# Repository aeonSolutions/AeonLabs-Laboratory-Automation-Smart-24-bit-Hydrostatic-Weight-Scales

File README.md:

[PCB-Prototyping-Catalogue](https://github.com/aeonSolutions/PCB-Prototyping-Catalogue)  >>  [Laboratory Automation](https://github.com/aeonSolutions/PCB-Prototyping-Catalogue/tree/main/Laboratory%20Automation)  >> Wieght Scales >> Smart 24-bit Hydrostatic Weight Scale

<br>

# 24-bit Smart data Acquisiton SDAD for Weight Measurments

This is a 24-bit S.D.A.D. weight scale capable to do hydrostatic weight measurments up to 20Kg. 

<br>

## Parts List
 - [S.D.A.D. hardware electronics](http://www.tindie.com/stores/aeonlabs)
 - [Plexiglass Clear Acrylic Board](https://s.click.aliexpress.com/e/_Ddi8Lh5)
 - [Load Cell HX711 ](https://s.click.aliexpress.com/e/_DBjevT1)
 - [aluminum flat hex socket countersunk head screw size M4 20mm](https://www.aliexpress.com/item/32964202588.html?spm=a2g0o.order_list.order_list_main.4.f3a61802ivrUvG)
 - [aluminum flat hex socket countersunk head screw size M5 20mm](https://www.aliexpress.com/item/32964202588.html?spm=a2g0o.order_list.order_list_main.4.f3a61802ivrUvG)
 - [connector Cable M8 waterproof 4-pin](https://s.click.aliexpress.com/e/_DCR6iBd)
 - [USB-C cable](https://s.click.aliexpress.com/e/_De4Q32X)

<br>

## Compatibility

<p align="center">

</p>

<br>

## What one additionally needs
- [USB to UART/USB TTL firmware burner for 5V and 3.3V MCUs ](https://github.com/aeonSolutions/PCB-Prototyping-Catalogue/blob/main/DIY-Maker/README.md)
- [Upgradable ESP32 MCU](https://github.com/aeonSolutions/AeonLabs-Upgradable-MCU-ESP32)

<br />
<br />

**Get a Notification on every PCB update**

|  | You can fill in your [email here (Google form)](https://docs.google.com/forms/d/e/1FAIpQLScErMgQYRdA-umvCjvTPPrCO7Lg1QYowTxb7vfa8cTfrcPEAA/viewform?usp=pp_url) and I'll send a reminder when a new PCB prototype is made available here or a new revision for an existing PCB. Stay tuned! |
|-------------|------|

<br>
<br>

## Author

You can get in touch with me on my LinkedIn Profile:

#### Miguel Tomas

You can also follow my GitHub Profile to stay updated about my latest projects: 

**Hire me on Fiverr**

If you like my work here and are looking to design and deploy your own smart device you can hire me on:

- [Fiverr](https://www.fiverr.com/s/GjmPxe). The price starts at $25
- [Guru](https://www.guru.com/freelancers/miguel-tomas)
  
<br>

### Be supportive of my dedication and work towards technology education and buy me a cup of coffee
The PCB Desgin Files i provide here for anyone to use are free. If you like this Smart Device or use it, please consider buying me a cup of coffee, a slice of pizza or a book to help me study, eat and think new PCB design files.

<br />

### Make a donation on Paypal
Make a donation on paypal and get a TAX refund*.

<br>

### Support all these open hardware projects and become a patreon  
Liked any of my PCB KiCad Designs? Help and Support my open work to all by becomming a LDAD Patreon.
In return I will give a free PCB design in KiCad to all patreon supporters. To learn more go to patreon.com. Link below.

<br />
<br />

______________________________________________________________________________________________________________________________
### License

Before proceeding to download any of AeonLabs software solutions for open-source development and/or PCB hardware electronics development make sure you are choosing the right license for your project. See [AeonLabs Solutions for Open Hardware & Source Development](https://github.com/aeonSolutions/PCB-Prototyping-Catalogue/wiki/AeonLabs-Solutions-for-Open-Hardware-&-Source-Development) for more information.

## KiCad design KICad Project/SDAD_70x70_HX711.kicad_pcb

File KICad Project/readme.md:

[PCB-Prototyping-Catalogue](https://github.com/aeonSolutions/PCB-Prototyping-Catalogue)  >>  [Laboratory Automation](https://github.com/aeonSolutions/PCB-Prototyping-Catalogue/tree/main/Laboratory%20Automation)  >> Wieght Scales >> Smart 24-bit Hydrostatic Weight Scale

<div align="right">
 <a href="https://github-com.translate.goog/aeonSolutions/AeonLabs-AI-Volvo-MKII-Open-Hardware/wiki?_x_tr_sl=en&_x_tr_tl=pt&_x_tr_hl=en&_x_tr_pto=wapp">Change language</a>  <br>
Last change 15-02-2024
</div>

<br>

This folder contains the KiCad project files for the Smart 24-bit Hydrostatic Weight Scales used on my Open Science projects. Each KiCad project is available with a [creative commons share alike non-commercial license](https://creativecommons.org/licenses/by-nc-sa/4.0/deed.en) . If you like it and use it on your own hardware designs please support this project, [click here](https://github.com/sponsors/aeonSolutions) to learn how. <br> Thank you 🙏. 

### Support all these open hardware projects and become a GitHub sponsor  
Liked any of my PCB KiCad Designs? Help and Support my open work to all by becoming a GitHub sponsor.

<p align="center">

</p>

#

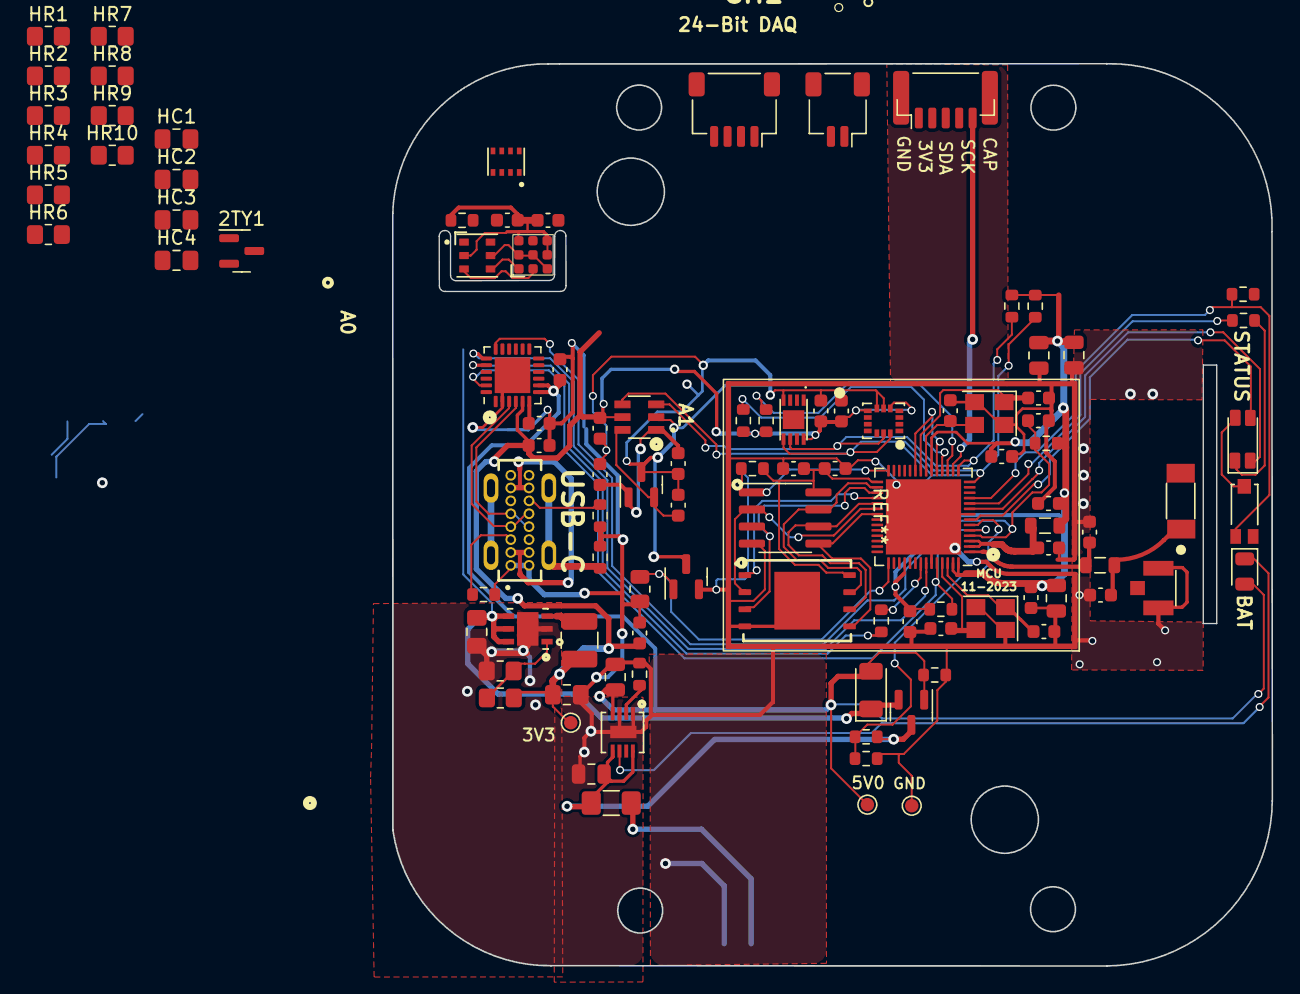
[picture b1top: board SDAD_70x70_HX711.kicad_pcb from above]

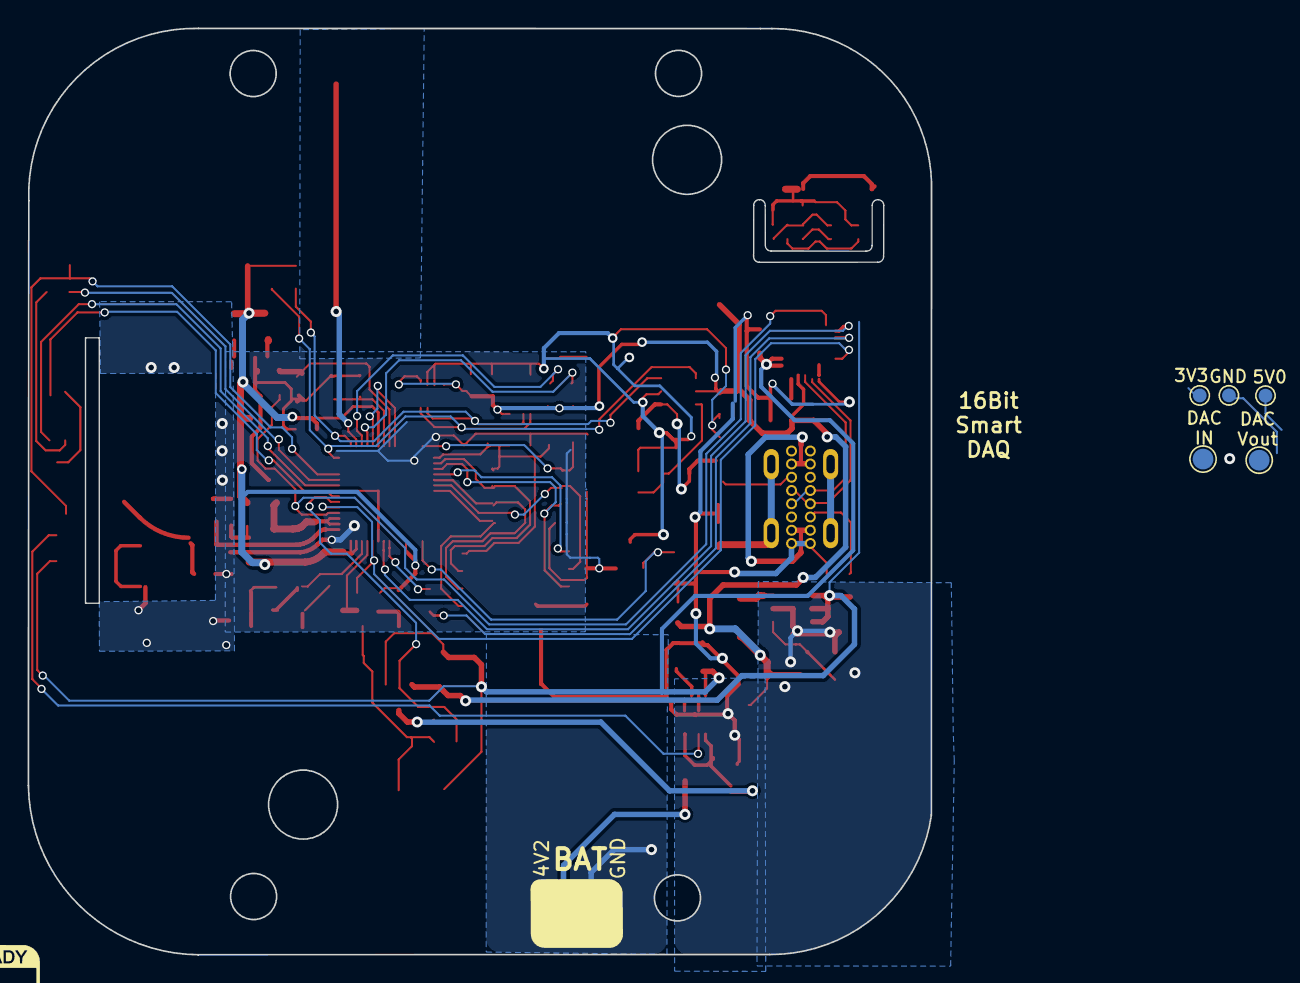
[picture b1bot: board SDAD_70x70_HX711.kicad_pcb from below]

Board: 2 copper layers, 65.4 x 67.1 mm, 108 parts (4 on the bottom side), 64 nets.

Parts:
2TY1: S8550; SOT-23
ADS1100_CH2: ADS1100A0IDBVR; ADS1100 16-bit ADC SOT95P280X145-6N
ADS1100_CH_C3: 33-100pF; C_0603_1608Metric
ADS1100_CH_C4: 100nF; C_0603_1608Metric
ATSHA_C1: 100nF; C_0603_1608Metric
AUR1: AUR9718x_DFN_3x3mm_6_pin; AUR9718 ST1S09 SON95P300X300X100-7N
AUR_C1: 22uF; C_0805_2012Metric_Pad1.18x1.45mm_HandSolder
AUR_C2: 4.7uF; C_0805_2012Metric_Pad1.18x1.45mm_HandSolder
AUR_R1: 75k; R_0805_2012Metric_Pad1.20x1.40mm_HandSolder
AUR_R2: 24k; R_0805_2012Metric_Pad1.20x1.40mm_HandSolder
AUR_l1: 3.3uF; L_1210_3225Metric
BAT_FUSE1: Polyfuse; Fuse_1206_3216Metric_Pad1.42x1.75mm_HandSolder
BAT_SENSE_R1, BAT_SENSE_R2: 100k; R_0603_1608Metric
BMPR1: 10k; R_0603_1608Metric
CHC1, CHC2, CHC3: 1uF; C_0603_1608Metric
CN3065_C2: 4.7uF; C_0805_2012Metric
CN3065_R1: 1K8; R_0603_1608Metric
CN3065_STDBY_LED1: LED; LED_0805_2012Metric
CN3965_C1: 22uF; C_0805_2012Metric
DMP1045U_1: DMP1045U; SOT-23
DMP1045_R1: 10K; R_0603_1608Metric
DMP1045_SCHOT1: D_Schottky; D_1206_3216Metric
ENS_C1: 1uF; C_0603_1608Metric
ENS_C2: 100nF; C_0603_1608Metric
EPS1: ESP32-PSRAM_LY68L6400S; SOIC-8_3.9x4.9mm_P1.27mm
ESP32S1: ESP32-S3; QFN-56-1EP_7x7mm_P0.4mm_EP5.6x5.6mm
ESP32_SHIELD1: RFShield_OnePiece; ESP32-S3 GND Shield
ESP_FLASH1: W25Q128JVS; WSON8 FLASH SPI SON127P800X600X80-9N
E_DTR_R1: 10k; R_0603_1608Metric
E_LNA_ANT1: AN9520; CrossAir CA-C03
E_LNA_ANT2: U.FL-R-SMT(01); RF Antenna IPEX SMD PCB HRS_U.FL-R-SMT(01)
E_LNA_C1, E_LNA_C2: 2.7pF; C_0603_1608Metric
E_LNA_l1: 1.8nH 5%; L_0805_2012Metric
E_RTS_C1: 100nF; C_0603_1608Metric
E_RTS_R1: 10k; R_0603_1608Metric
E_SPI_C1: 1uF 10% 50V; C_0603_1608Metric
E_SPI_C2: 100nF 10% 16V; C_0603_1608Metric
E_UART_TX_1: 499R; R_0603_1608Metric
E_VDDA_C1: 100nF; C_0603_1608Metric
E_VDDA_C2: 1uF 10% 50V; C_0805_2012Metric
E_VDD_3_C1, E_VDD_3_C2: 10uF 20% 6.3V; C_0805_2012Metric
E_VDD_3_C3, E_VDD_3_C4: 100nF 10% 16V; C_0603_1608Metric
E_VDD_CPU_C1: 100nF 10% 16V; C_0603_1608Metric
E_VDD_L1: 12nH 5%; L_0805_2012Metric
E_VDD_RTC_C1: 100nF 10% 16V; C_0603_1608Metric
E_XTAL32_1: 32.768Mhz 22pF+-10PPM; Crystal_SMD_3225-4Pin_3.2x2.5mm
E_XTAL32_C1, E_XTAL32_C2, E_XTAL40_C1, E_XTAL40_C2: 22pF 5% 50V; C_0603_1608Metric
E_XTAL40_1: 40Mhz 22pF+-10PPM; Crystal_SMD_3225-4Pin_3.2x2.5mm
ExtSWBAT_PLUG2: Conn_01x03_Female; JST_SH_BM03B-SRSS-TB_1x03-1MP_P1.00mm_Vertical
HC1: 10pF; C_0805_2012Metric_Pad1.18x1.45mm_HandSolder
HC2, HC3, HC4: 0.1pF; C_0805_2012Metric_Pad1.18x1.45mm_HandSolder
HR1, HR2, HR9, HR10: 2k2; R_0805_2012Metric_Pad1.20x1.40mm_HandSolder
HR3, HR4, HR7, HR8: 100R; R_0805_2012Metric_Pad1.20x1.40mm_HandSolder
HR5: 18k4; R_0805_2012Metric_Pad1.20x1.40mm_HandSolder
HR6: 8.4k; R_0805_2012Metric_Pad1.20x1.40mm_HandSolder
HXC2: 2.2uF; C_0603_1608Metric
I2C1: I2C6; JST_SH_SM04B-SRSS-TB_1x04-1MP_P1.00mm_Horizontal
I2C_SCL_R2, I2C_SDA_R1, I2C_SDA_R2, I2C_SDA_R2#2: 10k; R_0603_1608Metric
IC_ENS1: ENS160 Gas Semsor
IMU1: LSM6DS3; LSM6DS3 Motion Sensor PQFN50P300X250X86-14N
IMUC1: 100nF; C_0603_1608Metric
J2: USB4120-03-C_REVA; USB-C Vertical GCT_USB4120-03-C_REVA
LED1: LED_GBRC; LED_1206_3210_RGB_Metric
LR1: 330R; R_0603_1608Metric
MTRR1: 10k; R_0805_2012Metric
MTRT1: NPN; SOT-23
PLUG2: PLUG2; JST_SH_BM05B-SRSS-TB_1x05-1MP_P1.00mm_Vertical
PSRAM_R1: 100K; R_0603_1608Metric
PWOUT3V1: Screw_Terminal_01x02; JST_SH_SM02B-SRSS-TB_1x02-1MP_P1.00mm_Horizontal
TMPR1: 10K; R_0603_1608Metric
TP1, TP1#2: VIN; TestPoint_Pad_D1.0mm
TP2, TP2#2: VOut; TestPoint_Pad_D1.0mm
TP3, TP3#2: GND; TestPoint_Pad_D1.0mm
U1: MCP1525-TT; SOT-23
U2: ATSHA204A-MAHDA-T; ATSHA204A-MAHDA-T UDFN-8
U3: Battery_charger_CN3065_QFN8; QFN8 3.1x2.9mm QFNn-8 3x3 SON80P400X400X100-9N
U4: AHT20; AHT20 HT Sensor PSON100P300X300X110-6N
U5: CH9102F
U6: TEMT6000; TEMT6000-SEN
U7: BMP280; XDCR_BMP280
USB_PLUG_R2, USB_PLUG_R4: 5k1; R_0603_1608Metric
USB_PLYG_R1: 150K; R_0603_1608Metric
VOLTAGE_REF_C1, VOLTAGE_REF_C2: 100nF; C_0603_1608Metric

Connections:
3V3: 2TY1.2 (E), ADS1100_CH2.5 (VDD), ADS1100_CH_C4.2, ATSHA_C1.2, AUR_C1.1, AUR_R1.1, AUR_l1.1, BMPR1.2, CHC3.1, ENS_C1.2, ENS_C2.2, ESP32S1.20 (VDD3P3_RTC), ESP32S1.46 (VDD3P3_CPU), ESP32S1.55 (VDDA), ESP32S1.56 (VDDA), E_DTR_R1.1, E_RTS_R1.1, E_VDDA_C1.2, E_VDDA_C2.2, E_VDD_3_C1.1, E_VDD_3_C2.1, E_VDD_3_C3.1, E_VDD_CPU_C1.1, E_VDD_L1.1, E_VDD_RTC_C1.1, HXC2.2, I2C_SCL_R2.1, I2C_SDA_R1.2, I2C_SDA_R2.1, I2C_SDA_R2#2.2, IC_ENS1.4 (VDD), IC_ENS1.5 (VDDIO), IC_ENS1.7 (CS), IMU1.5 (VDDIO), IMU1.8 (VDD), IMUC1.2, LED1.4 (K), PLUG2.2, TP2.1, TP2#2.1, U2.8 (VCC), U4.2 (VDD), U5.5 (VIO), U6.COLLECTOR, U7.6 (VDDIO), U7.8 (VDD)
3V3_PLUG: ADS1100_CH2.1 (VIN+), ADS1100_CH_C3.2, U1.1 (Vin), VOLTAGE_REF_C1.2
A+: HR1.2, HR4.2, I2C1.3
A-: HR2.2, HR3.2, I2C1.4
B+: HR7.2, HR9.2, I2C1.1
B-: HR8.2, HR10.1, I2C1.2
BAT_SENSE_IO21: BAT_SENSE_R1.1, BAT_SENSE_R2.2, ESP32S1.6 (GPIO1/ADC1_CH0)
CAPACITIVE_SENSOR_IO11: ESP32S1.16 (GPIO11/ADC2_CH0), PLUG2.5
CHIP_EN: ESP32S1.4 (CHIP_PU/RESET), E_RTS_C1.2, E_RTS_R1.2, U5.18 (CTS)
DAC_CALIBRATION: ESP32S1.19 (GPIO14/ADC2_CH3), ESP32S1.23 (GPIO17/ADC2_CH6/DAC_2)
ESP_GPIO0_BOOT-DTR: ESP32S1.5 (GPIO0/BOOT), ESP32S1.52 (GPIO46), E_DTR_R1.2, U5.23 (DTR)
GND: AUR1.2 (GND), AUR1.7 (GND), AUR_C1.2, AUR_C2.2, AUR_R2.2, BAT_SENSE_R1.2, CHC1.2, CHC2.1, CHC3.2, CN3065_C2.1, CN3065_R1.1, CN3965_C1.1, DMP1045_R1.2, EPS1.4 (VSS), ESP32S1.8 (GPIO3/ADC1_CH2), ESP32S1.51 (GPIO45), ESP32S1.57 (GND), ESP32_SHIELD1.1 (Shield), ESP_FLASH1.4 (GND), ESP_FLASH1.9 (GND), E_LNA_ANT2.1 (GND), E_LNA_ANT2.2 (GND), E_LNA_C1.2, E_LNA_C2.2, E_RTS_C1.1, E_SPI_C1.2, E_SPI_C2.2, E_VDDA_C1.1, E_VDDA_C2.1, E_VDD_3_C1.2, E_VDD_3_C2.2, E_VDD_3_C3.2, E_VDD_3_C4.2, E_VDD_CPU_C1.2, E_VDD_RTC_C1.2, E_XTAL32_1.2, E_XTAL32_1.4, E_XTAL32_C1.2, E_XTAL32_C2.2, E_XTAL40_1.2, E_XTAL40_1.4, E_XTAL40_C1.2, E_XTAL40_C2.2, ExtSWBAT_PLUG2.3, HC1.1, HC2.2, HR2.1, HR6.2, HR10.2, HXC2.1, J2.A1 (GND_A), J2.A12 (GND_A__1), J2.B1 (GND_B), J2.B12 (GND_B__1), MTRR1.1, MTRT1.2, PWOUT3V1.2, TP3.1, TP3#2.1, U3.1 (V_Temp), U3.3 (GND), U3.9 (GND), U5.0 (GND), U5.2 (GND), USB_PLUG_R2.2, USB_PLUG_R4.2, USB_PLYG_R1.2
GNDD: ADS1100_CH2.2 (GND), ADS1100_CH_C3.1, ADS1100_CH_C4.1, ATSHA_C1.1, ENS_C1.1, ENS_C2.1, IC_ENS1.3 (MISO), IC_ENS1.8 (VSS), IC_ENS1.9 (VSS), IMU1.6 (GND), IMU1.7 (GND), IMUC1.1, MTRT1.3, PLUG2.1, TMPR1.1, U1.3 (Vss), U2.4 (GND), U4.5 (GND), U7.1 (GND), U7.5 (SDO), U7.7 (GND), VOLTAGE_REF_C1.1, VOLTAGE_REF_C2.1
GPIO8_I2C_SDA: ADS1100_CH2.4 (SDA), ESP32S1.14 (GPIO9/ADC1_CH8), I2C_SDA_R1.1, IC_ENS1.1 (SDA), IMU1.14 (SDA), PLUG2.3, U2.5 (SDA), U4.4 (SDA), U7.3 (SDI)
GPIO9_I2C_SCL: ADS1100_CH2.3 (SCL), ESP32S1.15 (GPIO10/ADC1_CH9), I2C_SDA_R2.2, IC_ENS1.2 (SCL), IMU1.13 (SCL), PLUG2.4, U2.6 (SCL), U4.3 (SCL), U7.4 (SCK)
HX3V3: 2TY1.3 (C), HC1.2, HR1.1, HR5.2, HR9.1, PWOUT3V1.1
LCD_I2C_SCL_IO12: ESP32S1.18 (GPIO13/ADC2_CH2), I2C_SCL_R2.2
LCD_I2C_SDA_IO38: ESP32S1.17 (GPIO12/ADC2_CH1), I2C_SDA_R2#2.1
LED_B_IO05: ESP32S1.7 (GPIO2/ADC1_CH1), LED1.2 (BA)
LED_G_IO02: ESP32S1.9 (GPIO4/ADC1_CH3), LED1.1 (GA)
LED_R_IO04: ESP32S1.10 (GPIO5/ADC1_CH4), LR1.1
unnamed: AUR1.1 (FB), AUR_R1.2, AUR_R2.1
unnamed: AUR1.3 (SW), AUR_l1.2
unnamed: ESP32S1.21 (GPIO15/ADC2_CH4/XTAL_32K_P), E_XTAL32_1.3, E_XTAL32_C1.1
unnamed: ESP32S1.22 (GPIO16/ADC2_CH5/XTAL_32K_N), E_XTAL32_1.1, E_XTAL32_C2.1
unnamed: ESP32S1.1 (LNA_IN/RF), E_LNA_C2.1, E_LNA_l1.2
unnamed: ESP32S1.49 (U0TXD/PROG/GPIO43), E_UART_TX_1.2
unnamed: ESP32S1.2 (VDD3P3), ESP32S1.3 (VDD3P3), E_VDD_3_C4.1, E_VDD_L1.2
unnamed: ESP32S1.53 (XTAL_N), E_XTAL40_1.3, E_XTAL40_C2.1
unnamed: ESP32S1.54 (XTAL_P), E_XTAL40_1.1, E_XTAL40_C1.1
unnamed: E_LNA_ANT1.1, E_LNA_C1.1, E_LNA_l1.1
unnamed: HC3.2, HR4.1
unnamed: HC3.1, HR3.1
unnamed: HC4.2, HR7.1
unnamed: HC4.1, HR8.1
unnamed: HR5.1, HR6.1
unnamed: J2.A5 (CC1), USB_PLUG_R2.1
unnamed: J2.B5 (CC2), USB_PLUG_R4.1
unnamed: J2.S1 (SHIELD), USB_PLYG_R1.1
unnamed: LED1.3 (RA), LR1.2
unnamed: CN3065_R1.2, U3.2 (I_SET)
unnamed: CHC2.2, U5.6 (V3)
unnamed: BMPR1.1, U7.2 (CSB)
PERIPHERALS_PWR_EN_IO38: ESP32S1.43 (GPIO38), MTRR1.2, MTRT1.1
RXD0: ESP32S1.50 (U0RXD/PROG/GPIO44), U5.19 (RTS)
SPICLK: EPS1.6 (SCLK), ESP32S1.33 (SPICLK/GPIO30), ESP_FLASH1.6 (CLK)
SPICS0: ESP32S1.32 (SPICS0/GPIO29), ESP_FLASH1.1 (~CS)
SPICS1: EPS1.1 (~CE), ESP32S1.28 (SPI_CS1/GPIO26), PSRAM_R1.1
SPID: EPS1.5 (SiO0), ESP32S1.35 (SPID/GPIO32), ESP_FLASH1.5 (DI(IO0))
SPIHD: EPS1.7 (SIO3), ESP32S1.30 (SPIHD/GPIO27), ESP_FLASH1.7 (IO3)
SPIQ: EPS1.2 (SIO1), ESP32S1.34 (SPIQ/GPIO31), ESP_FLASH1.2 (DO(IO1))
SPIWP: EPS1.3 (SIO2), ESP32S1.31 (SPIWP/GPIO28), ESP_FLASH1.3 (IO2)
STDBY_LED_G: CN3065_STDBY_LED1.1 (K), U3.6 (LED_DONE)
TEMT6000_IO33: ESP32S1.11 (GPIO6/ADC1_CH5), TMPR1.2, U6.EMITTER
TXD0: E_UART_TX_1.1, U5.20 (RXD)
USB_5V0: CHC1.1, CN3065_STDBY_LED1.2 (A), CN3965_C1.2, DMP1045U_1.1, DMP1045_R1.1, DMP1045_SCHOT1.2 (A), TP1.1, U3.4 (VIN), U5.7 (VDD5), U5.8 (VBUS)
USB_5V0F: J2.A4 (VBUS_A), J2.A9 (VBUS_A__1), J2.B4 (VBUS_B), J2.B9 (VBUS_B__1)
USB_D+: J2.A6 (D1+), J2.B6 (D2+), U5.3 (D+)
USB_D-: J2.A7 (D1-), J2.B7 (D2-), U5.4 (D-)
VDD_SPI: EPS1.8 (VCC), ESP32S1.29 (VDD_SPI), ESP_FLASH1.8 (VCC), E_SPI_C1.1, E_SPI_C2.1, PSRAM_R1.2
VIN: AUR1.4 (VIN_SW), AUR1.5 (VIN_A), AUR1.6 (EN), AUR_C2.1, DMP1045U_1.2, DMP1045_SCHOT1.1 (K), TP1#2.1
VIN_BAT: BAT_FUSE1.1, BAT_SENSE_R2.1, CN3065_C2.2, DMP1045U_1.3, U3.5 (BAT+), U3.8 (FB)
VIN_BATF: BAT_FUSE1.2, ExtSWBAT_PLUG2.1
VOLTAGE_REF_2.5V: ADS1100_CH2.6 (VIN-), U1.2 (Vout), VOLTAGE_REF_C2.2

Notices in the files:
KICad Project/SDAD_70x70_HX711.kicad_pcb:
Creative Commons non commercial share alike
